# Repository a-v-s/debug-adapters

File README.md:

# debug-adapters
Debug Adapters (JTAG/SWD) for various debuggers and cables

Dongles
-------

A number of adapters for various dongles to the 1.27mm 10 pin "Cortex" debugger connector.

Adapters for various Debug dongles:

* ST-Link SWDIO - GND - SWDCLK - 3V3 - 5V
* ST-Link SWDCLK - SWDIO - GND - 3V3 - 5V
* ST-Link "Baite"
* Altera / Atmel pinout

20 PIN JTAG 
-----------

Standard 20 Pin JTAG, as found on J-Link, ST-Link, etc.

This adapter boards allows to connect:
* "Cortex" debugger connector
* 6 pin SWD (for tag connect)
* RJ-12 SWD (for tag connect)
* SWD PIN Header
* UART PIN header

On a J-Link V9+, when using SWD, it offers a UART. 
For this a UART header is offered. Take note that 
while the ST-Link may offer an UART as well, it is
on different pins and will not work with that adapter.

For FTDI based debuggers, there is a jumper to enable SWD.
Take care to place and remote this jumper when changing
protocols on an FTDI based adapter. Do not place this
jumper with other deugger types.

This board offers the possibility to supply the target
with a selectable voltage. For this feature to work,
one must supply voltage on pin 19.

Target power on J-Link
---------------------
The J-Link is capable to supply 5 Volts on Pin 19.
This can be enabled and disabled in Software

Using J-Link Commander:
```
power on
```
or to make it permanenet

```
power on perm
```

Using OpenOCD:
```
jlink config targetpower on
```

Please note that most clones will output 3.3 Volt on pin 1 by default. One must open the unit and remove a jumper to disable this "feature". 
Also take care to verify a clone does implement level shifting at all when using a target at a lower voltage.

Target Power on ST-Link
-----------------------

The ST-Link outputs 3.3 Volts on pin 19. As such, to supply the target with 3.3 Volts, use the VSupply settings rather then the 3.3 Setting.

Note that the ST-Link will only shift the incoming signals, as ST microcontrollers can handle 3.3 volts when
running at lower voltages. Be aware of this when using ST-LINK with other microcontrollers.

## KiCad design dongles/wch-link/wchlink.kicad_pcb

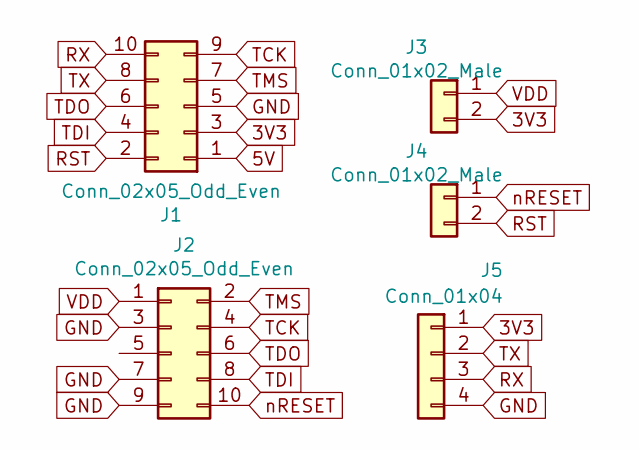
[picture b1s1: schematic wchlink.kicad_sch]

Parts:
J1: Conn_02x05_Odd_Even; PinSocket_2x05_P2.54mm_Horizontal
J2: Conn_02x05_Odd_Even; PinHeader_2x05_P1.27mm_Vertical
J3, J4: Conn_01x02_Male; PinHeader_1x02_P2.54mm_Vertical
J5: Conn_01x04; PinHeader_1x04_P2.54mm_Vertical

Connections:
3V3: J1.3, J3.2, J5.1
5V: J1.1
GND: J1.5, J2.3, J2.7, J2.9, J5.4
RST: J1.2, J4.2
RX: J1.10, J5.3
TCK: J1.9, J2.4
TDI: J1.4, J2.8
TDO: J1.6, J2.6
TMS: J1.7, J2.2
TX: J1.8, J5.2
VDD: J2.1, J3.1
nRESET: J2.10, J4.1

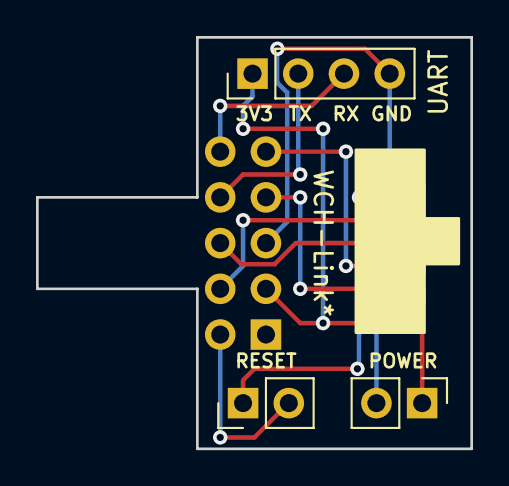
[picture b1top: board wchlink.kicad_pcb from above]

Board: 2 copper layers, 24.1 x 22.9 mm, 5 parts (1 on the bottom side), 11 nets.

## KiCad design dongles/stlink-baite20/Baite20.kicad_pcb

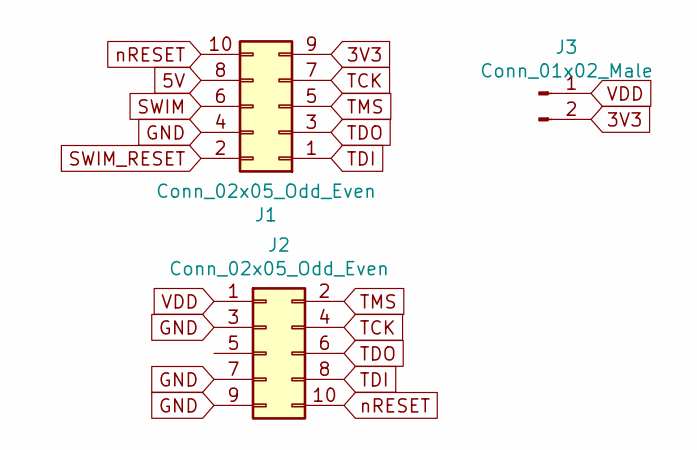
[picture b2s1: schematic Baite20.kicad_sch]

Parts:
J1: Conn_02x05_Odd_Even; PinSocket_2x05_P2.54mm_Horizontal
J2: Conn_02x05_Odd_Even; PinHeader_2x05_P1.27mm_Vertical
J3: Conn_01x02_Male; PinHeader_1x02_P2.54mm_Vertical

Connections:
3V3: J1.9, J3.2
5V: J1.8
GND: J1.4, J2.3, J2.7, J2.9
SWIM: J1.6
SWIM_RESET: J1.2
TCK: J1.7, J2.4
TDI: J1.1, J2.8
TDO: J1.3, J2.6
TMS: J1.5, J2.2
VDD: J2.1, J3.1
nRESET: J1.10, J2.10

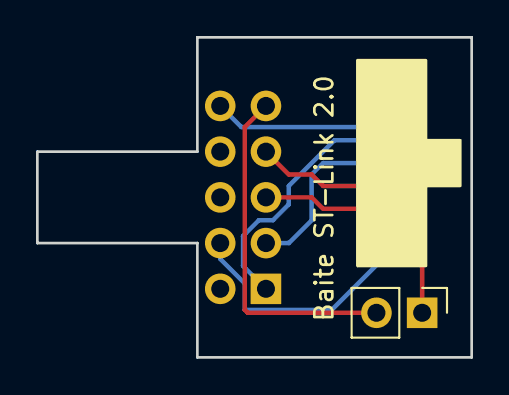
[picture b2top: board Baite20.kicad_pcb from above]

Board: 2 copper layers, 24.1 x 17.8 mm, 3 parts (1 on the bottom side), 8 nets.

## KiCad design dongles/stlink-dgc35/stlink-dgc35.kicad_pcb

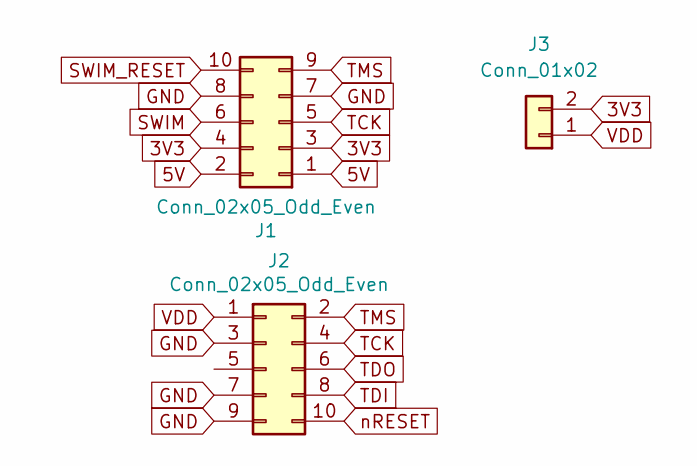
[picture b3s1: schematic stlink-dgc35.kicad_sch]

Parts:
J1: Conn_02x05_Odd_Even; PinSocket_2x05_P2.54mm_Horizontal
J2: Conn_02x05_Odd_Even; PinHeader_2x05_P1.27mm_Vertical
J3: Conn_01x02; PinHeader_1x02_P2.54mm_Vertical

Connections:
3V3: J1.3, J1.4, J3.2
5V: J1.1, J1.2
GND: J1.7, J1.8, J2.3, J2.7, J2.9
SWIM: J1.6
SWIM_RESET: J1.10
TCK: J1.5, J2.4
TDI: J2.8
TDO: J2.6
TMS: J1.9, J2.2
VDD: J2.1, J3.1
nRESET: J2.10

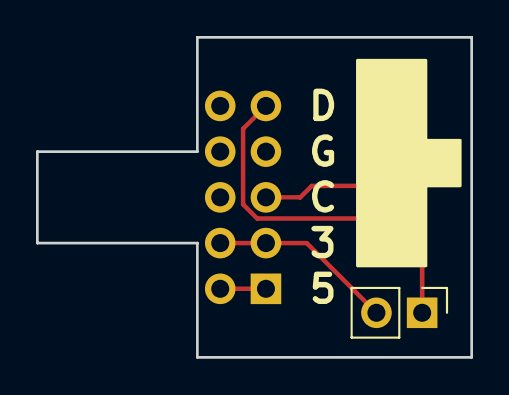
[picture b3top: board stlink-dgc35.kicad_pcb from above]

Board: 2 copper layers, 24.1 x 17.8 mm, 3 parts (1 on the bottom side), 6 nets.

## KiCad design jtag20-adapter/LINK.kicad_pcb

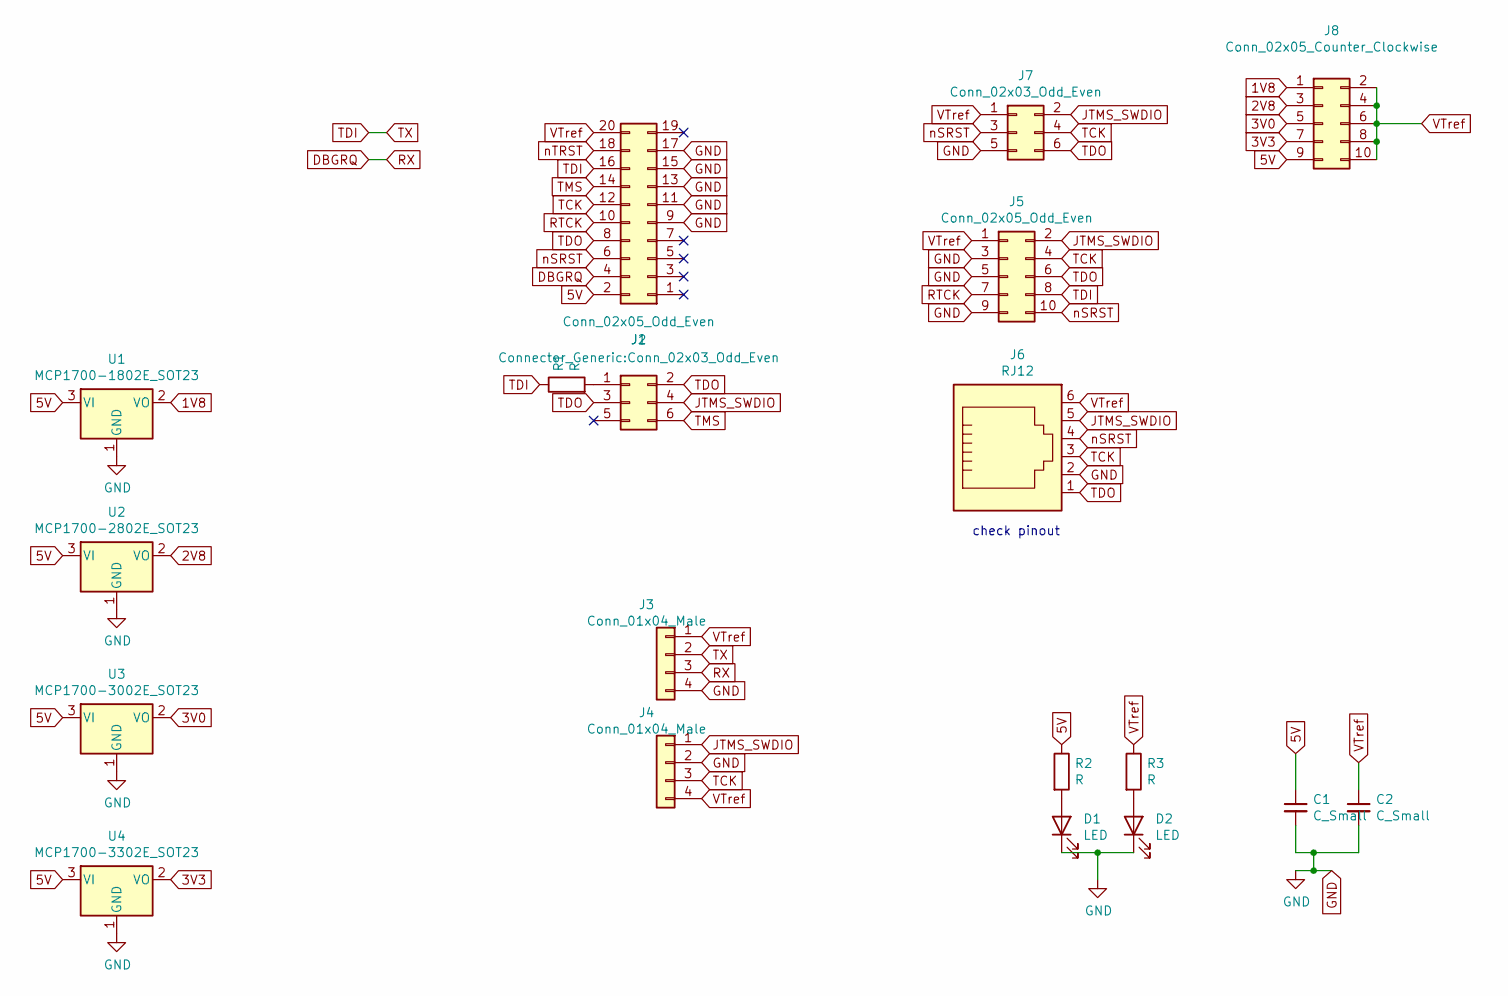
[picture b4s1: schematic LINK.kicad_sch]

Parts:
C1, C2: C_Small; C_0805_2012Metric_Pad1.18x1.45mm_HandSolder
D1, D2: LED; LED_0805_2012Metric_Pad1.15x1.40mm_HandSolder
J1: Conn_02x05_Odd_Even; PinSocket_2x10_P2.54mm_Horizontal
J2: Connector_Generic:Conn_02x03_Odd_Even; PinHeader_2x03_P2.54mm_Vertical
J3, J4: Conn_01x04_Male; PinHeader_1x04_P2.54mm_Vertical
J5: Conn_02x05_Odd_Even; PinHeader_2x05_P1.27mm_Vertical
J6: RJ12
J7: Conn_02x03_Odd_Even; PinHeader_2x03_P2.54mm_Vertical
J8: Conn_02x05_Counter_Clockwise; PinHeader_2x05_P2.54mm_Vertical
R1, R2, R3: R; R_0805_2012Metric_Pad1.20x1.40mm_HandSolder
U1: MCP1700-1802E_SOT23; SOT-23
U2: MCP1700-2802E_SOT23; SOT-23
U3: MCP1700-3002E_SOT23; SOT-23
U4: MCP1700-3302E_SOT23; SOT-23

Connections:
1V8: J8.1, U1.2 (VO)
2V8: J8.3, U2.2 (VO)
3V0: J8.5, U3.2 (VO)
3V3: J8.7, U4.2 (VO)
5V: C1.1, J1.2, J8.9, R2.1, U1.3 (VI), U2.3 (VI), U3.3 (VI), U4.3 (VI)
DBGRQ: J1.4, J3.3
GND: C1.2, C2.2, D1.1 (K), D2.1 (K), J1.9, J1.11, J1.13, J1.15, J1.17, J3.4, J4.2, J5.3, J5.5, J5.9, J6.2, J7.5, U1.1 (GND), U2.1 (GND), U3.1 (GND), U4.1 (GND)
JTMS_SWDIO: J2.4, J4.1, J5.2, J6.5, J7.2
unnamed: D1.2 (A), R2.2
unnamed: D2.2 (A), R3.2
unnamed: J2.1, R1.2
RTCK: J1.10, J5.7
TCK: J1.12, J4.3, J5.4, J6.3, J7.4
TDI: J1.16, J3.2, J5.8, R1.1
TDO: J1.8, J2.2, J2.3, J5.6, J6.1, J7.6
TMS: J1.14, J2.6
VTref: C2.1, J1.20, J3.1, J4.4, J5.1, J6.6, J7.1, J8.2, J8.4, J8.6, J8.8, J8.10, R3.1
nSRST: J1.6, J5.10, J6.4, J7.3
nTRST: J1.18

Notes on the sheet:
check pinout

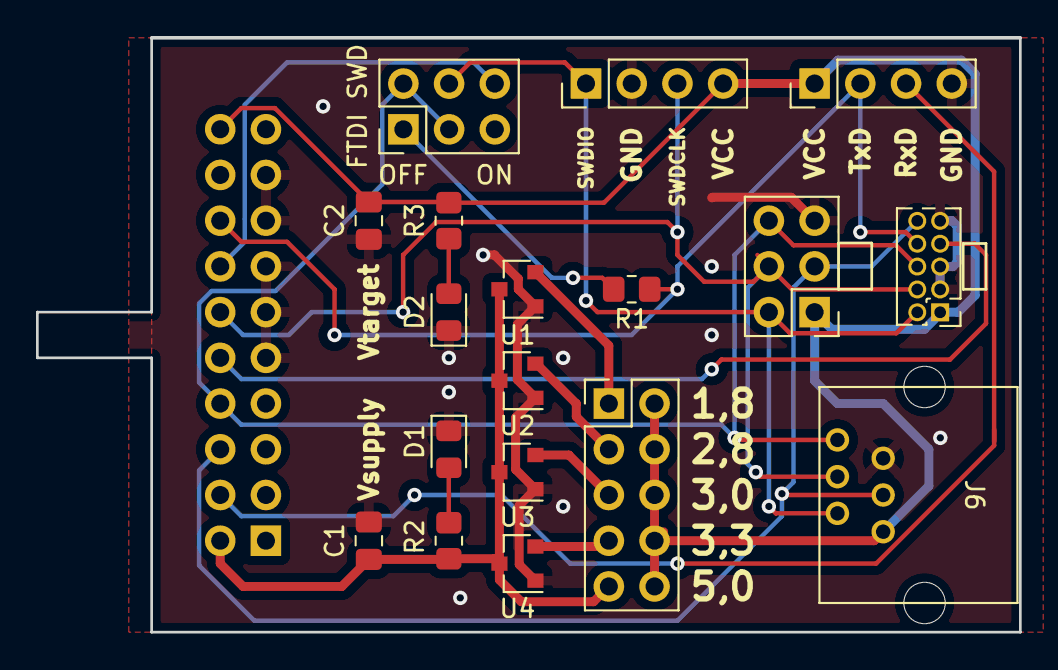
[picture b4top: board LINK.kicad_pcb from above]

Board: 2 copper layers, 54.6 x 33.0 mm, 19 parts (1 on the bottom side), 18 nets.

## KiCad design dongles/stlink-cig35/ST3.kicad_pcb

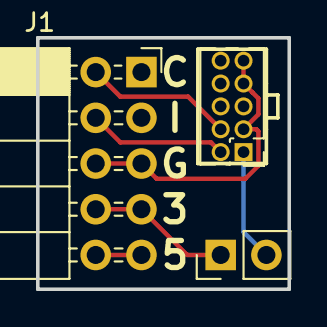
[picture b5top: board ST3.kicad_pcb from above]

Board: 2 copper layers, 14.0 x 14.0 mm, 3 parts (0 on the bottom side), 6 nets.

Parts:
J1: Conn_02x05_Odd_Even; PinSocket_2x05_P2.54mm_Horizontal
J2: Conn_02x05_Odd_Even; PinHeader_2x05_P1.27mm_Vertical
J3: Conn_01x02_Male; PinHeader_1x02_P2.54mm_Vertical

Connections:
3V3: J1.7, J1.8, J3.1
5V: J1.9, J1.10
GND: J1.5, J1.6, J2.3, J2.7, J2.9
TCK: J1.2, J2.4
TMS: J1.4, J2.2
VDD: J2.1, J3.2

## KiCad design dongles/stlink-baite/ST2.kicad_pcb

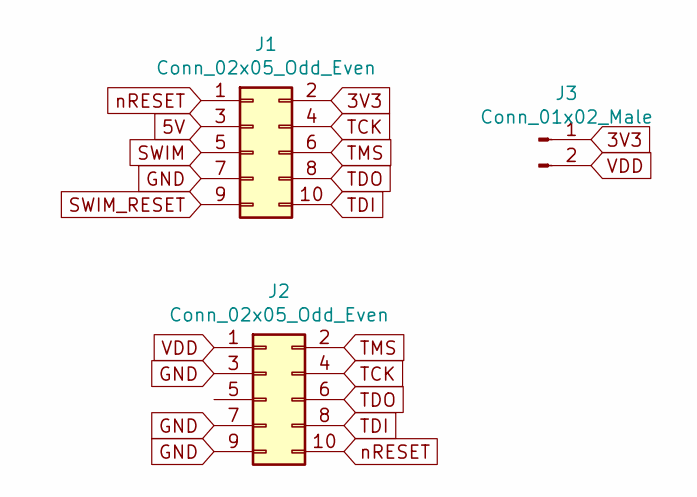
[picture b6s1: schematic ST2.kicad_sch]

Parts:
J1: Conn_02x05_Odd_Even; PinSocket_2x05_P2.54mm_Horizontal
J2: Conn_02x05_Odd_Even; PinHeader_2x05_P1.27mm_Vertical
J3: Conn_01x02_Male; PinHeader_1x02_P2.54mm_Vertical

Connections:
3V3: J1.2, J3.1
5V: J1.3
GND: J1.7, J2.3, J2.7, J2.9
SWIM: J1.5
SWIM_RESET: J1.9
TCK: J1.4, J2.4
TDI: J1.10, J2.8
TDO: J1.8, J2.6
TMS: J1.6, J2.2
VDD: J2.1, J3.2
nRESET: J1.1, J2.10

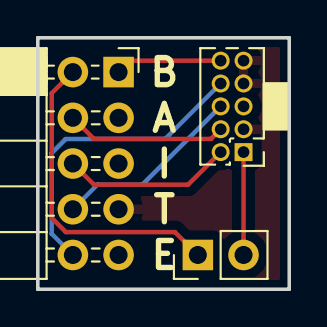
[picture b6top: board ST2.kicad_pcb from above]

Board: 2 copper layers, 14.0 x 14.0 mm, 3 parts (0 on the bottom side), 8 nets.

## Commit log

2018-11-18 v2.0: Removed 1v5 LDO, added SWD connector, Rotated 10pinJTAG
2018-11-18 Added silkscreen label
2018-12-28 V2: Rotated VDD jumper + a little wider
2022-02-11 V2.1
2022-02-11 V2.1 Gerbers
2022-02-13 Update new design
2022-02-13 Altera
2022-02-13 ST-Link Baite
2022-02-13 ST-Link CIG
2022-02-13 ST-Link IGC
2022-02-13 20 pin JTAG adapter
2022-02-20 fixing FTDI SWD support
2022-02-20 fixing connector name
2022-03-04 v2.2
2022-03-04 LINK-V2.3
2026-05-16 Add gerbers for Dongle Adapters v2.0
2026-05-16 WCH-Link adapter v2.1
